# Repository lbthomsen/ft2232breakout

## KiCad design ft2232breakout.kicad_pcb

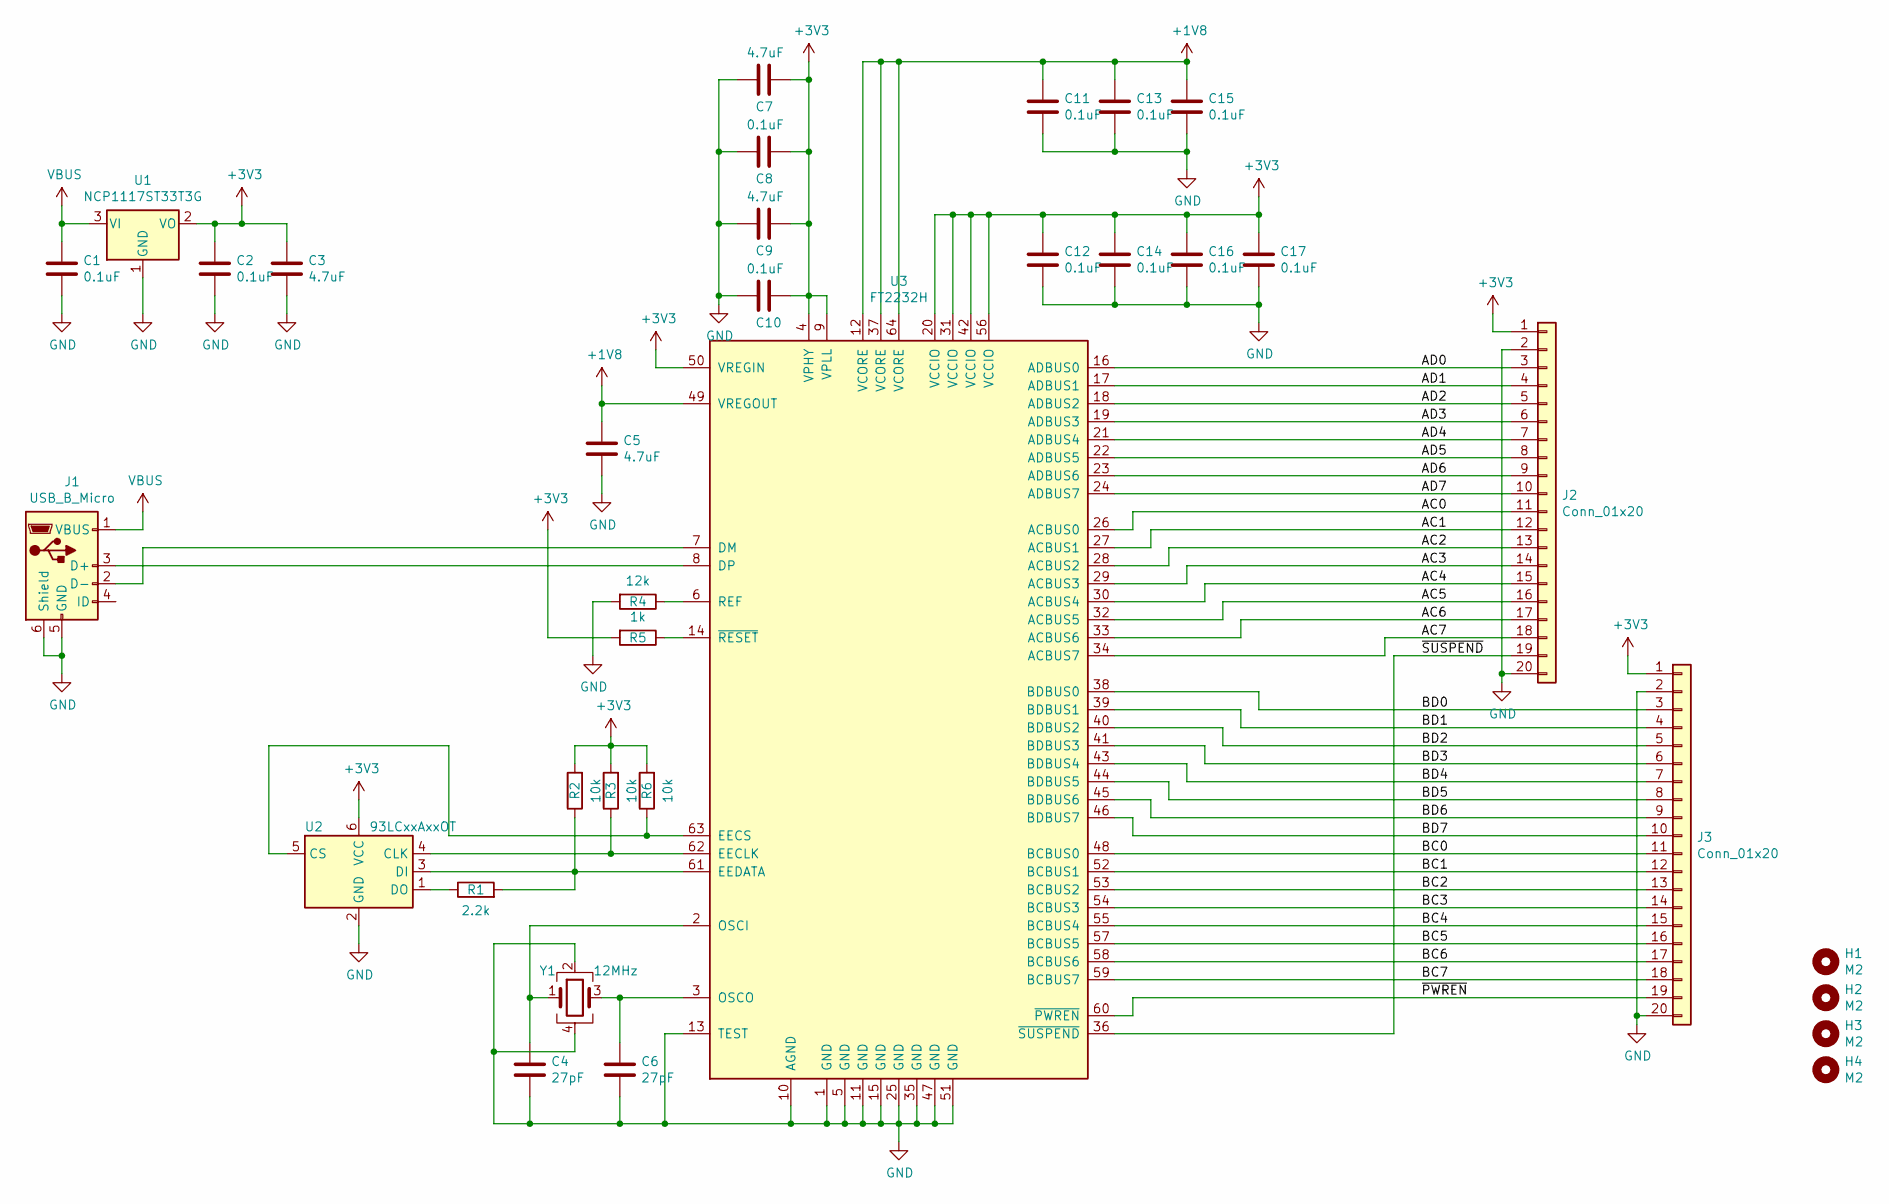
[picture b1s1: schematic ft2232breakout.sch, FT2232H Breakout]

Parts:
C1, C2, C8, C10, C11, C12, C13, C14, C15, C16, C17: 0.1uF; C_0603_1608Metric; Digikey 1276-1000-1-ND
C3, C5, C7, C9: 4.7uF; C_0603_1608Metric; Digikey 1276-6684-1-ND
C4, C6: 27pF; C_0603_1608Metric; Digikey 1276-2247-1-ND
H1, H2, H3, H4: M2; MountingHole_2.2mm_M2
J1: USB_B_Micro; USB_Micro-B_Molex-105017-0001; Digikey WM1399CT-ND
J2, J3: Conn_01x20; PinHeader_2x10_P2.54mm_Vertical
R1: 2.2k; R_0603_1608Metric
R2, R3, R6: 10k; R_0603_1608Metric
R4: 12k; R_0603_1608Metric
R5: 1k; R_0603_1608Metric
U1: NCP1117ST33T3G; SOT-223-3_TabPin2
U2: 93LCxxAxxOT; SOT-23-6
U3: FT2232H; LQFP-64_10x10mm_P0.5mm; Digikey 768-1024-2-ND
Y1: 12MHz; Crystal_SMD_3225-4Pin_3.2x2.5mm_HandSoldering

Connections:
+1V8: C5.1, C11.1, C13.1, C15.1, U3.12 (VCORE), U3.37 (VCORE), U3.49 (VREGOUT), U3.64 (VCORE)
+3V3: C2.1, C3.1, C7.1, C8.1, C9.1, C10.1, C12.1, C14.1, C16.1, C17.1, J2.1, J3.1, R2.2, R3.2, R5.2, R6.2, U1.2 (VO), U2.6 (VCC), U3.4 (VPHY), U3.9 (VPLL), U3.20 (VCCIO), U3.31 (VCCIO), U3.42 (VCCIO), U3.50 (VREGIN), U3.56 (VCCIO)
/AC0: J2.11, U3.26 (ACBUS0)
/AC1: J2.12, U3.27 (ACBUS1)
/AC2: J2.13, U3.28 (ACBUS2)
/AC3: J2.14, U3.29 (ACBUS3)
/AC4: J2.15, U3.30 (ACBUS4)
/AC5: J2.16, U3.32 (ACBUS5)
/AC6: J2.17, U3.33 (ACBUS6)
/AC7: J2.18, U3.34 (ACBUS7)
/AD0: J2.3, U3.16 (ADBUS0)
/AD1: J2.4, U3.17 (ADBUS1)
/AD2: J2.5, U3.18 (ADBUS2)
/AD3: J2.6, U3.19 (ADBUS3)
/AD4: J2.7, U3.21 (ADBUS4)
/AD5: J2.8, U3.22 (ADBUS5)
/AD6: J2.9, U3.23 (ADBUS6)
/AD7: J2.10, U3.24 (ADBUS7)
/BC0: J3.11, U3.48 (BCBUS0)
/BC1: J3.12, U3.52 (BCBUS1)
/BC2: J3.13, U3.53 (BCBUS2)
/BC3: J3.14, U3.54 (BCBUS3)
/BC4: J3.15, U3.55 (BCBUS4)
/BC5: J3.16, U3.57 (BCBUS5)
/BC6: J3.17, U3.58 (BCBUS6)
/BC7: J3.18, U3.59 (BCBUS7)
/BD0: J3.3, U3.38 (BDBUS0)
/BD1: J3.4, U3.39 (BDBUS1)
/BD2: J3.5, U3.40 (BDBUS2)
/BD3: J3.6, U3.41 (BDBUS3)
/BD4: J3.7, U3.43 (BDBUS4)
/BD5: J3.8, U3.44 (BDBUS5)
/BD6: J3.9, U3.45 (BDBUS6)
/BD7: J3.10, U3.46 (BDBUS7)
/~PWREN: J3.19, U3.60 (~PWREN)
/~SUSPEND: J2.19, U3.36 (~SUSPEND)
GND: C1.2, C2.2, C3.2, C4.2, C5.2, C6.2, C7.2, C8.2, C9.2, C10.2, C11.2, C12.2, C13.2, C14.2, C15.2, C16.2, C17.2, J1.5 (GND), J1.6 (Shield), J2.2, J2.20, J3.2, J3.20, R4.2, U1.1 (GND), U2.2 (GND), U3.1 (GND), U3.5 (GND), U3.10 (AGND), U3.11 (GND), U3.13 (TEST), U3.15 (GND), U3.25 (GND), U3.35 (GND), U3.47 (GND), U3.51 (GND), Y1.2, Y1.4
unnamed: C4.1, U3.2 (OSCI), Y1.1
unnamed: C6.1, U3.3 (OSCO), Y1.3
unnamed: J1.2 (D-), U3.7 (DM)
unnamed: J1.3 (D+), U3.8 (DP)
unnamed: R1.1, U2.1 (DO)
unnamed: R1.2, R2.1, U2.3 (DI), U3.61 (EEDATA)
unnamed: R3.1, U2.4 (CLK), U3.62 (EECLK)
unnamed: R4.1, U3.6 (REF)
unnamed: R5.1, U3.14 (~RESET)
unnamed: R6.1, U2.5 (CS), U3.63 (EECS)
VBUS: C1.1, J1.1 (VBUS), U1.3 (VI)

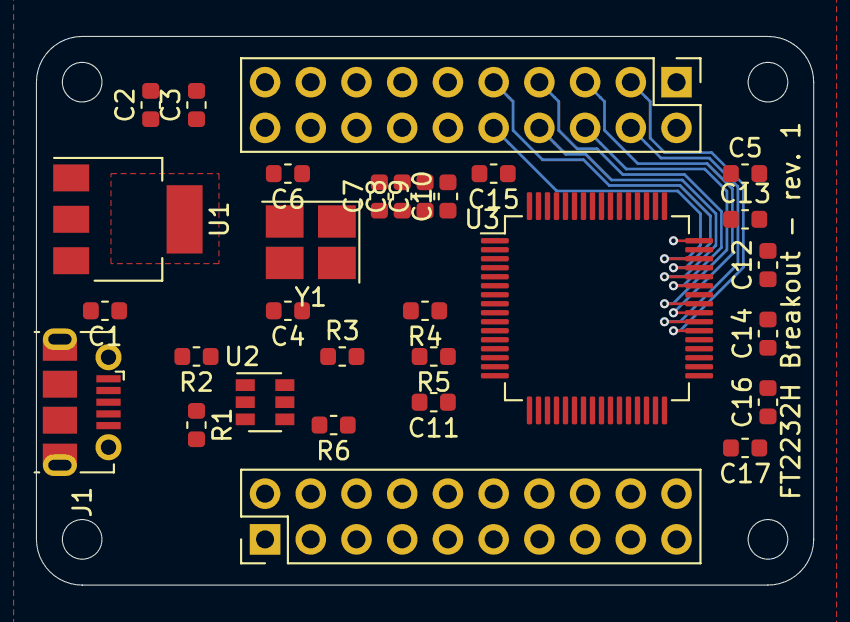
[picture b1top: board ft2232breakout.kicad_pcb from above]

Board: 2 copper layers, 43.2 x 30.5 mm, 34 parts (0 on the bottom side), 48 nets.

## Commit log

2019-05-30 Nearly there
2019-08-06 Made board smaller
2019-08-07 Hmmm
2019-08-07 Hmmmm
